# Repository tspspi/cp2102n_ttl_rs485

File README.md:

# Simple CP2102N USB to TTL and half duplex RS485 board

There is an [accompanying blog article](https://www.tspi.at/2023/05/27/cp2102basics.html) 
that explains the reasoning behind the design of this interface board.

This repository contains a simple open breakout board for the CP2102N. It uses
a simple bus powered design. All unused pins of the CP2102N are exposed via a
16 pin pin-header so one can easily access them to experiment with the more advanced
features of the chip itself. In addition the board contains two LEDs on the GPIO.0
and GPIO.1 pins for TX and RX indication. For RS485 mode it also houses a single
MAX485 and utilizes the CP2102Ns toggle function for transmit and receive switching
on the MAX485. The bus can be optionally terminated with a 120 Ohm resistor by
setting a jumper. Note that the RS485 bus is _not_ galvanically isolated by a
transformer!

One can switch between TTL and RS485 operation by setting JP1 and JP2 accordingly.

## Files

The provided files are:

* The [KiCad](https://www.kicad.org/) sources in ```kicad/cp2102rs485```
* The Gerber production files in the ```gerber``` directory

## License

See [LICENSE.md](./LICENSE.md)

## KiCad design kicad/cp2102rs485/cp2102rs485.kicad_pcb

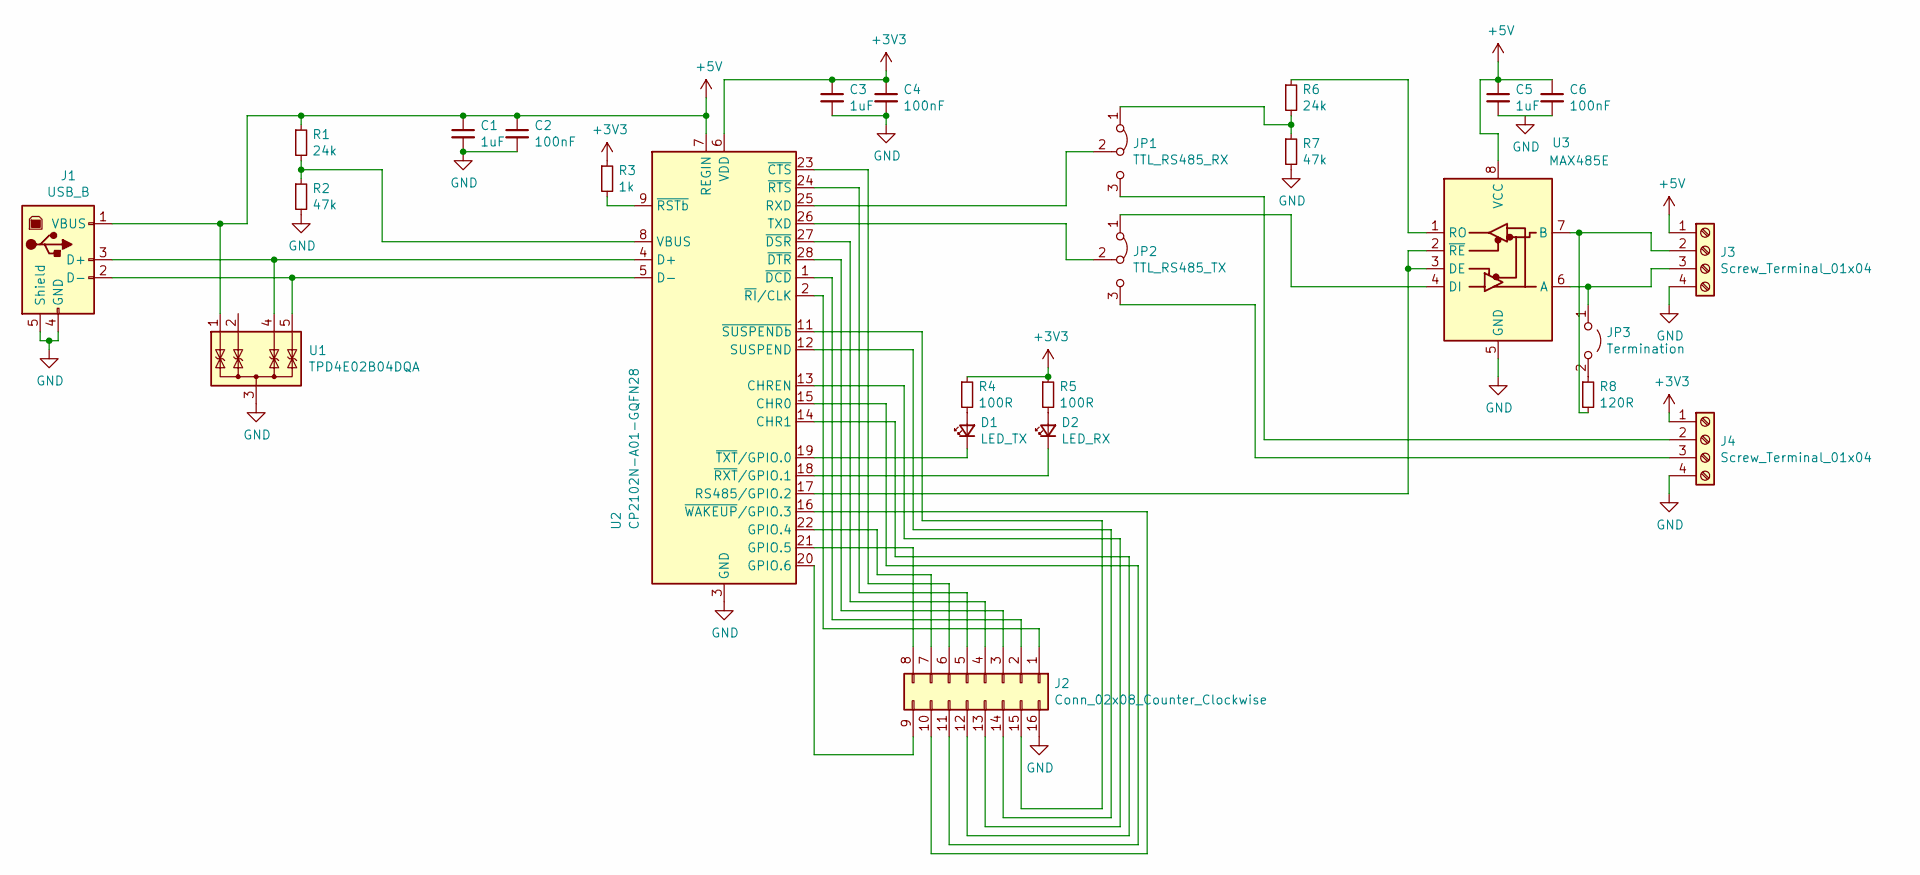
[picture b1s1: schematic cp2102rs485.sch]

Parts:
C1, C3, C5: 1uF; C_0805_2012Metric
C2, C4, C6: 100nF; C_0805_2012Metric
D1: LED_TX; LED_0805_2012Metric
D2: LED_RX; LED_0805_2012Metric
J1: USB_B; Wurth61400416121; MouserNR 710-61400416121
J2: Conn_02x08_Counter_Clockwise; PinHeader_2x08_P2.54mm_Vertical
J3, J4: Screw_Terminal_01x04; PinHeader_1x04_P2.54mm_Vertical
JP1: TTL_RS485_RX; PinHeader_1x03_P2.54mm_Vertical
JP2: TTL_RS485_TX; PinHeader_1x03_P2.54mm_Vertical
JP3: Termination; PinHeader_1x02_P2.54mm_Vertical
R1, R6: 24k; R_0805_2012Metric
R2, R7: 47k; R_0805_2012Metric
R3: 1k; R_0805_2012Metric
R4, R5: 100R; R_0805_2012Metric
R8: 120R; R_0805_2012Metric
U1: TPD4E02B04DQA; USON-10_2.5x1.0mm_P0.5mm
U2: CP2102N-A01-GQFN28; QFN-28-1EP_5x5mm_P0.5mm_EP3.35x3.35mm
U3: MAX485E; SO-8_3.9x4.9mm_P1.27mm; MouserNR 700-MAX485ESAT

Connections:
+3V3: C3.1, C4.1, J4.1, R3.1, R4.1, R5.1, U2.6 (VDD)
+5V: C1.1, C2.1, C5.1, C6.1, J1.1 (VBUS), J3.1, R1.1, U1.1 (IO1), U2.7 (REGIN), U3.8 (VCC)
unnamed: D1.1 (K), U2.19 (~TXT~/GPIO.0)
unnamed: D1.2 (A), R4.2
unnamed: D2.1 (K), U2.18 (~RXT~/GPIO.1)
unnamed: D2.2 (A), R5.2
unnamed: J1.2 (D-), U1.5 (IO4), U2.5 (D-)
unnamed: J1.3 (D+), U1.4 (IO3), U2.4 (D+)
unnamed: J2.1, U2.2 (~RI~/CLK)
unnamed: J2.2, U2.1 (~DCD)
unnamed: J2.3, U2.28 (~DTR)
unnamed: J2.4, U2.27 (~DSR)
unnamed: J2.5, U2.24 (~RTS)
unnamed: J2.6, U2.23 (~CTS)
unnamed: J2.7, U2.22 (GPIO.4)
unnamed: J2.8, U2.21 (GPIO.5)
unnamed: J2.9, U2.20 (GPIO.6)
unnamed: J2.10, U2.16 (~WAKEUP~/GPIO.3)
unnamed: J2.11, U2.15 (CHR0)
unnamed: J2.12, U2.14 (CHR1)
unnamed: J2.13, U2.13 (CHREN)
unnamed: J2.14, U2.12 (SUSPEND)
unnamed: J2.15, U2.11 (~SUSPENDb)
unnamed: J3.2, R8.2, U3.7 (B)
unnamed: J3.3, JP3.1 (A), U3.6 (A)
unnamed: J4.2, JP1.3 (B)
unnamed: J4.3, JP2.3 (B)
unnamed: JP1.1 (A), R6.2, R7.1
unnamed: JP1.2 (C), U2.25 (RXD)
unnamed: JP2.1 (A), U3.4 (DI)
unnamed: JP2.2 (C), U2.26 (TXD)
unnamed: JP3.2 (B), R8.1
unnamed: R1.2, R2.1, U2.8 (VBUS)
unnamed: R3.2, U2.9 (~RSTb)
unnamed: R6.1, U3.1 (RO)
unnamed: U2.17 (RS485/GPIO.2), U3.2 (~RE), U3.3 (DE)

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
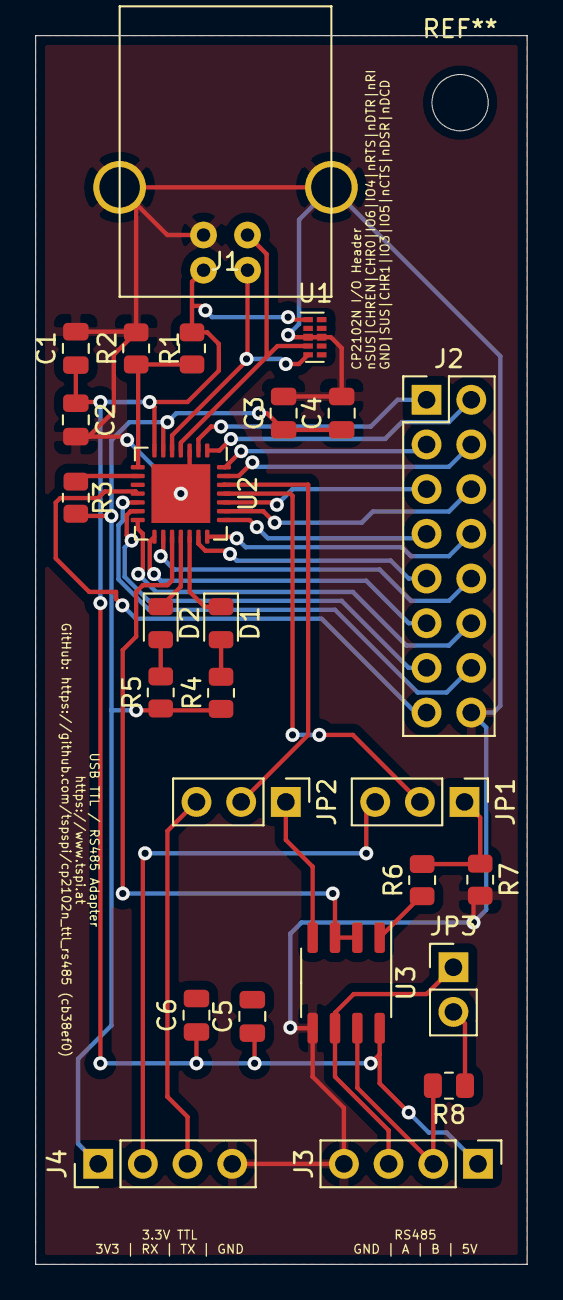
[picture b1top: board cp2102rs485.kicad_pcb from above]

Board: 2 copper layers, 27.9 x 69.9 mm, 26 parts (0 on the bottom side), 38 nets.

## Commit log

2023-04-23 Update labeling to reflect commit number
2023-04-23 Adding Gerber files
2023-04-23 Adding two renderings
2023-04-23 Readme, license, supress autosave
2023-05-27 Adding link to blog article
